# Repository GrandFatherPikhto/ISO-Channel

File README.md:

# ISO Channel v0.99 — fabrication files

A small isolated output board for the HiPIMS controller. It drives the trigger inputs of oscilloscopes,
sensors and similar loads. Generated with KiCad 10.0.8 from `Channel.kicad_pcb`.

The fabrication files are in `gerber/`, and `gerber-iso-channel.zip` holds the same files.

## Board

| Parameter | Value |
|---|---|
| Layers | 2 |
| Size | 55.05 × 59.48 mm, rectangle |
| Thickness | 1.6 mm, FR4 |
| Copper | 35 µm (1 oz), both sides — the layer stack is not set in the design |
| Min track / clearance | 0.2 / 0.2 mm |
| Min drill | 0.3 mm (vias) |
| Vias (pad / drill) | 19 × 0.6 / 0.3, 1 × 0.8 / 0.4 mm |
| Plated holes | components 0.7–1.0 mm; 1 × 3.5 mm (mounting hole H4) |
| Non-plated holes | 3 × 3.5 mm (mounting holes H1–H3) — separate file |
| Slots / oblong holes | none |
| Components | top side only |
| Impedance control | not required |
| Surface finish, colours | not specified in the design — choose at order |

## Files

| File | Content |
|---|---|
| `Channel-F_Cu.gtl` | Top copper |
| `Channel-B_Cu.gbl` | Bottom copper |
| `Channel-F_Mask.gts` | Top solder mask |
| `Channel-B_Mask.gbs` | Bottom solder mask |
| `Channel-F_Silkscreen.gto` | Top silkscreen |
| `Channel-B_Silkscreen.gbo` | Bottom silkscreen (empty) |
| `Channel-F_Paste.gtp` | Top paste — stencil only |
| `Channel-B_Paste.gbp` | Bottom paste (empty) |
| `Channel-Edge_Cuts.gm1` | Board outline |
| `Channel-PTH.drl` | Plated holes, Excellon, metric |
| `Channel-NPTH.drl` | Non-plated holes, Excellon, metric |
| `Channel-job.gbrjob` | Gerber job file |
| `Channel-PTH-drl_map.gbr`, `Channel-NPTH-drl_map.gbr` | Drill maps — for reference only, not needed for fabrication |

Gerber RS-274X (X2 attributes), units mm, format 4.6. All layers share the same origin.

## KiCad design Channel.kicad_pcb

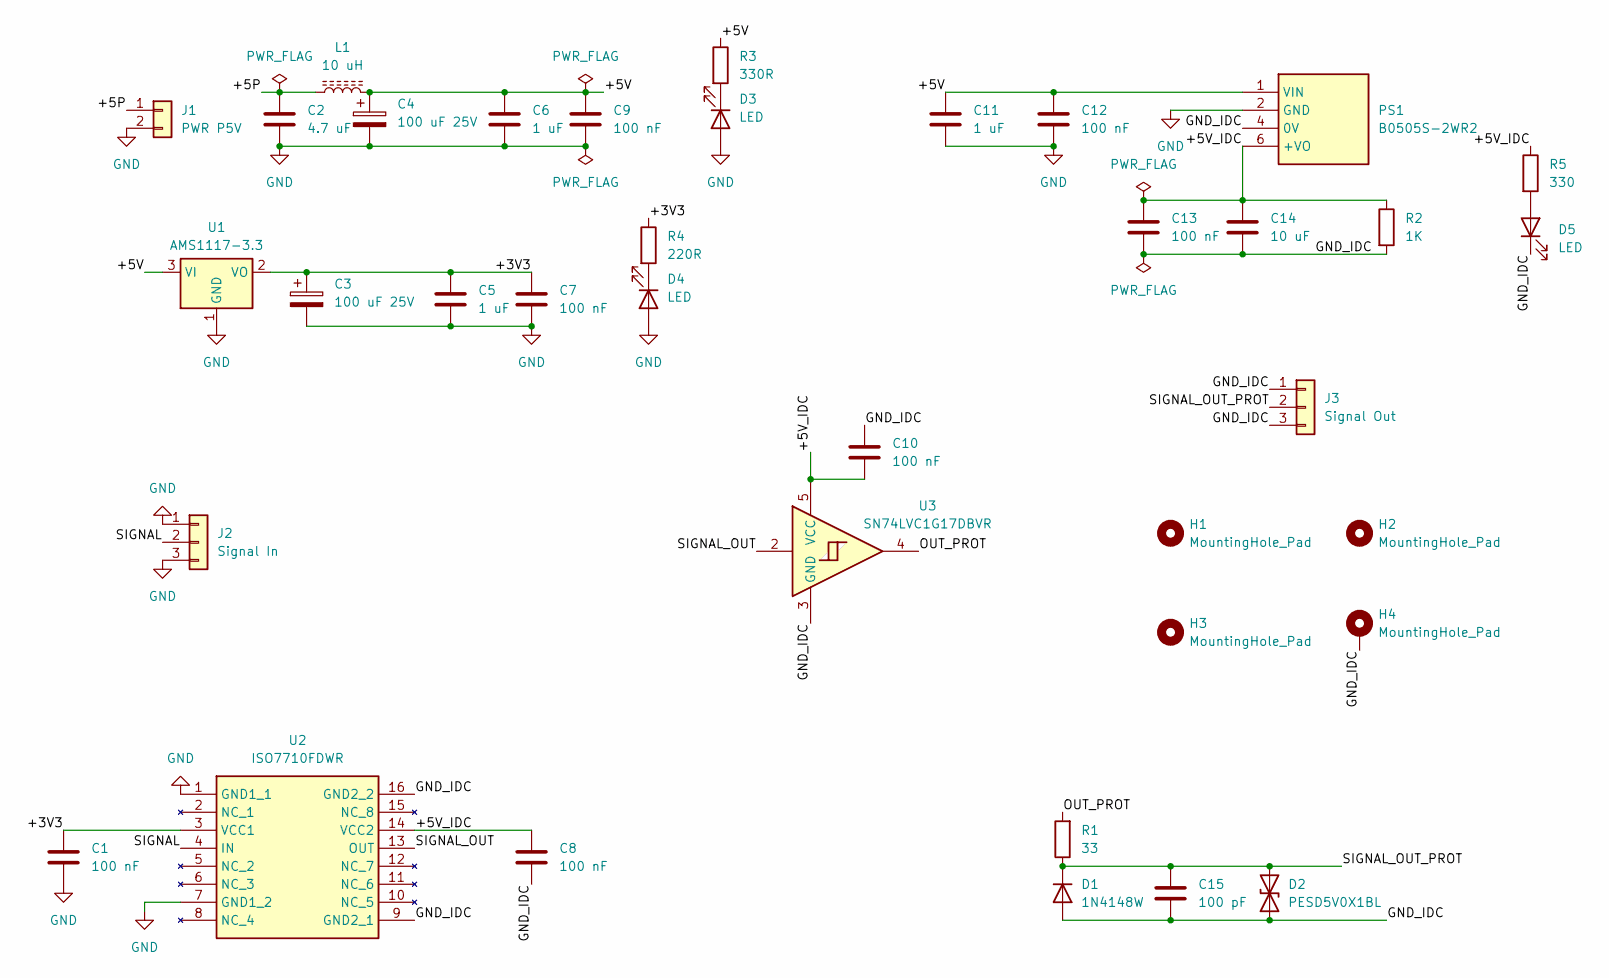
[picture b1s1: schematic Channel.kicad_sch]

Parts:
C1, C7, C8, C9, C10, C12, C13: 100 nF; C_0402_1005Metric_Pad0.74x0.62mm_HandSolder
C2: 4.7 uF; C_0603_1608Metric_Pad1.08x0.95mm_HandSolder
C3, C4: 100 uF 25V; CP_Radial_D5.0mm_P2.00mm
C5, C6, C11: 1 uF; C_0603_1608Metric_Pad1.08x0.95mm_HandSolder
C14: 10 uF; C_0603_1608Metric_Pad1.08x0.95mm_HandSolder
C15: 100 pF; C_0402_1005Metric_Pad0.74x0.62mm_HandSolder
D1: 1N4148W; D_SOD-123
D2: PESD5V0X1BL; D_SOD-882D
D3, D4, D5: LED; LED_0805_2012Metric_Pad1.15x1.40mm_HandSolder
H1, H2, H3: MountingHole_Pad; MountingHole_3.5mm
H4: MountingHole_Pad; MountingHole_3.5mm_Pad
J1: PWR P5V; JST_XH_B2B-XH-A_1x02_P2.50mm_Vertical
J2: Signal In; JST_XH_B3B-XH-A_1x03_P2.50mm_Vertical
J3: Signal Out; JST_XH_B3B-XH-A_1x03_P2.50mm_Vertical
L1: 10 uH; L_Bourns-SRN4018
PS1: B0505S-2WR2; SIP-4_19.65x7.05mm_P2.54mm; Manufacturer_Part_Number B0505S-2WR2
R1: 33; R_0402_1005Metric_Pad0.72x0.64mm_HandSolder
R2: 1K; R_1206_3216Metric_Pad1.30x1.75mm_HandSolder
R3: 330R; R_0402_1005Metric_Pad0.72x0.64mm_HandSolder
R4: 220R; R_0402_1005Metric_Pad0.72x0.64mm_HandSolder
R5: 330; R_0402_1005Metric_Pad0.72x0.64mm_HandSolder
U1: AMS1117-3.3; SOT-223-3_TabPin2
U2: ISO7710FDWR; SOIC-16W_7.5x10.3mm_P1.27mm
U3: SN74LVC1G17DBVR; SOT-23-5

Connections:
/+3V3: C1.1, C3.1, C5.1, C7.1, R4.1, U1.2 (VO), U2.3 (VCC1)
/+5P: C2.1, J1.1, L1.1
/+5V: C4.1, C6.1, C9.1, C11.1, C12.1, L1.2, PS1.1 (VIN), R3.1, U1.3 (VI)
/+5V_IDC: C8.1, C10.2, C13.1, C14.1, PS1.6 (+VO), R2.1, R5.1, U2.14 (VCC2), U3.5 (VCC)
/GND_IDC: C8.2, C10.1, C13.2, C14.2, C15.2, D1.2 (A), D2.1 (A1), D5.1 (K), H4.1 (1_1), J3.1, J3.3, PS1.4 (0V), R2.2, U2.9 (GND2_1), U2.16 (GND2_2), U3.3 (GND)
/OUT_PROT: R1.2, U3.4
/SIGNAL: J2.2, U2.4 (IN)
/SIGNAL_OUT: U2.13 (OUT), U3.2
/SIGNAL_OUT_PROT: C15.1, D1.1 (K), D2.2 (A2), J3.2, R1.1
GND: C1.2, C2.2, C3.2, C4.2, C5.2, C6.2, C7.2, C9.2, C11.2, C12.2, D3.2 (A), D4.2 (A), J1.2, J2.1, J2.3, PS1.2 (GND), U1.1 (GND), U2.1 (GND1_1), U2.7 (GND1_2)
unnamed: D3.1 (K), R3.2
unnamed: D4.1 (K), R4.2
unnamed: D5.2 (A), R5.2

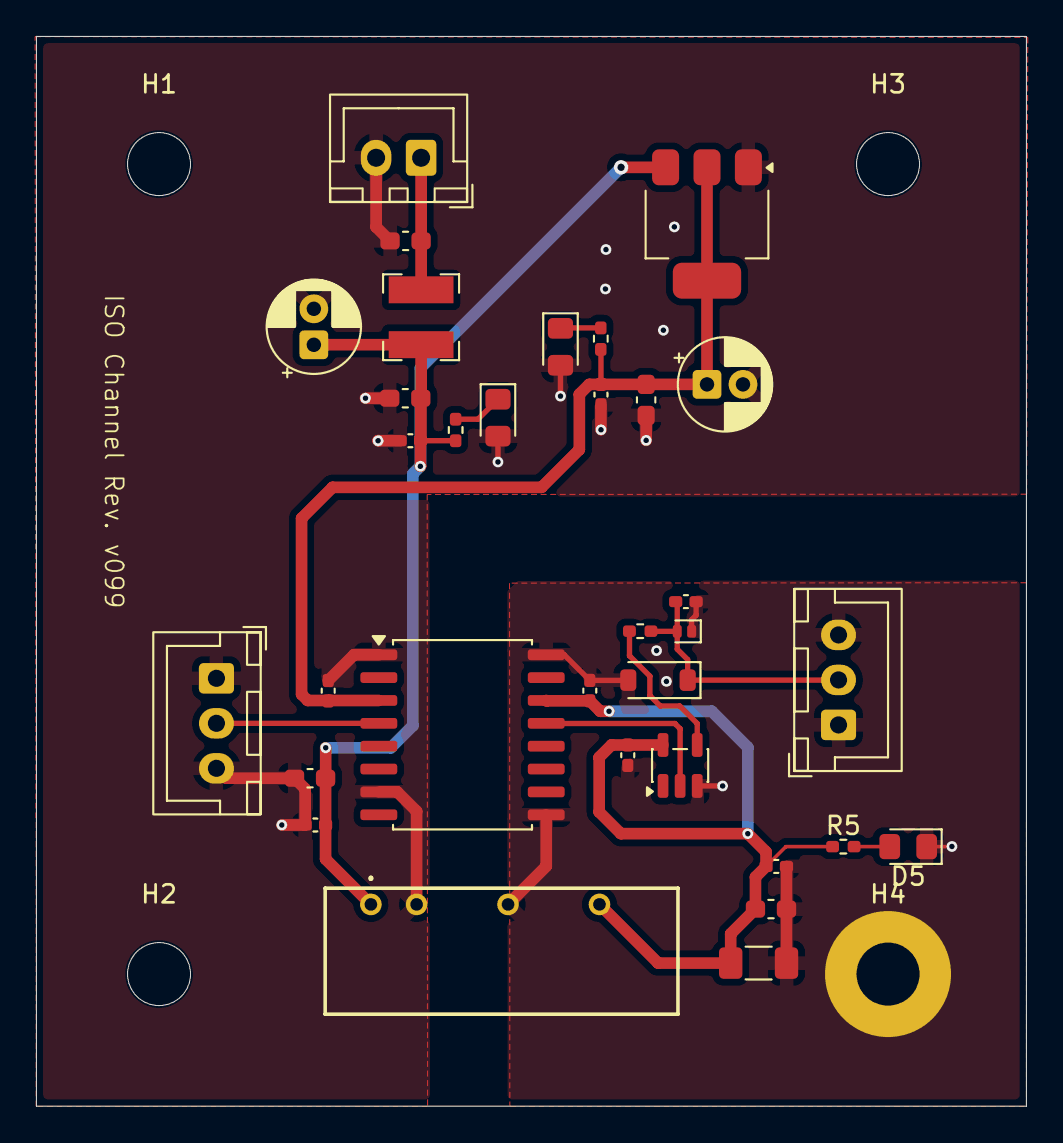
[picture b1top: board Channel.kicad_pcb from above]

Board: 2 copper layers, 55.0 x 59.4 mm, 37 parts (0 on the bottom side), 13 nets.
